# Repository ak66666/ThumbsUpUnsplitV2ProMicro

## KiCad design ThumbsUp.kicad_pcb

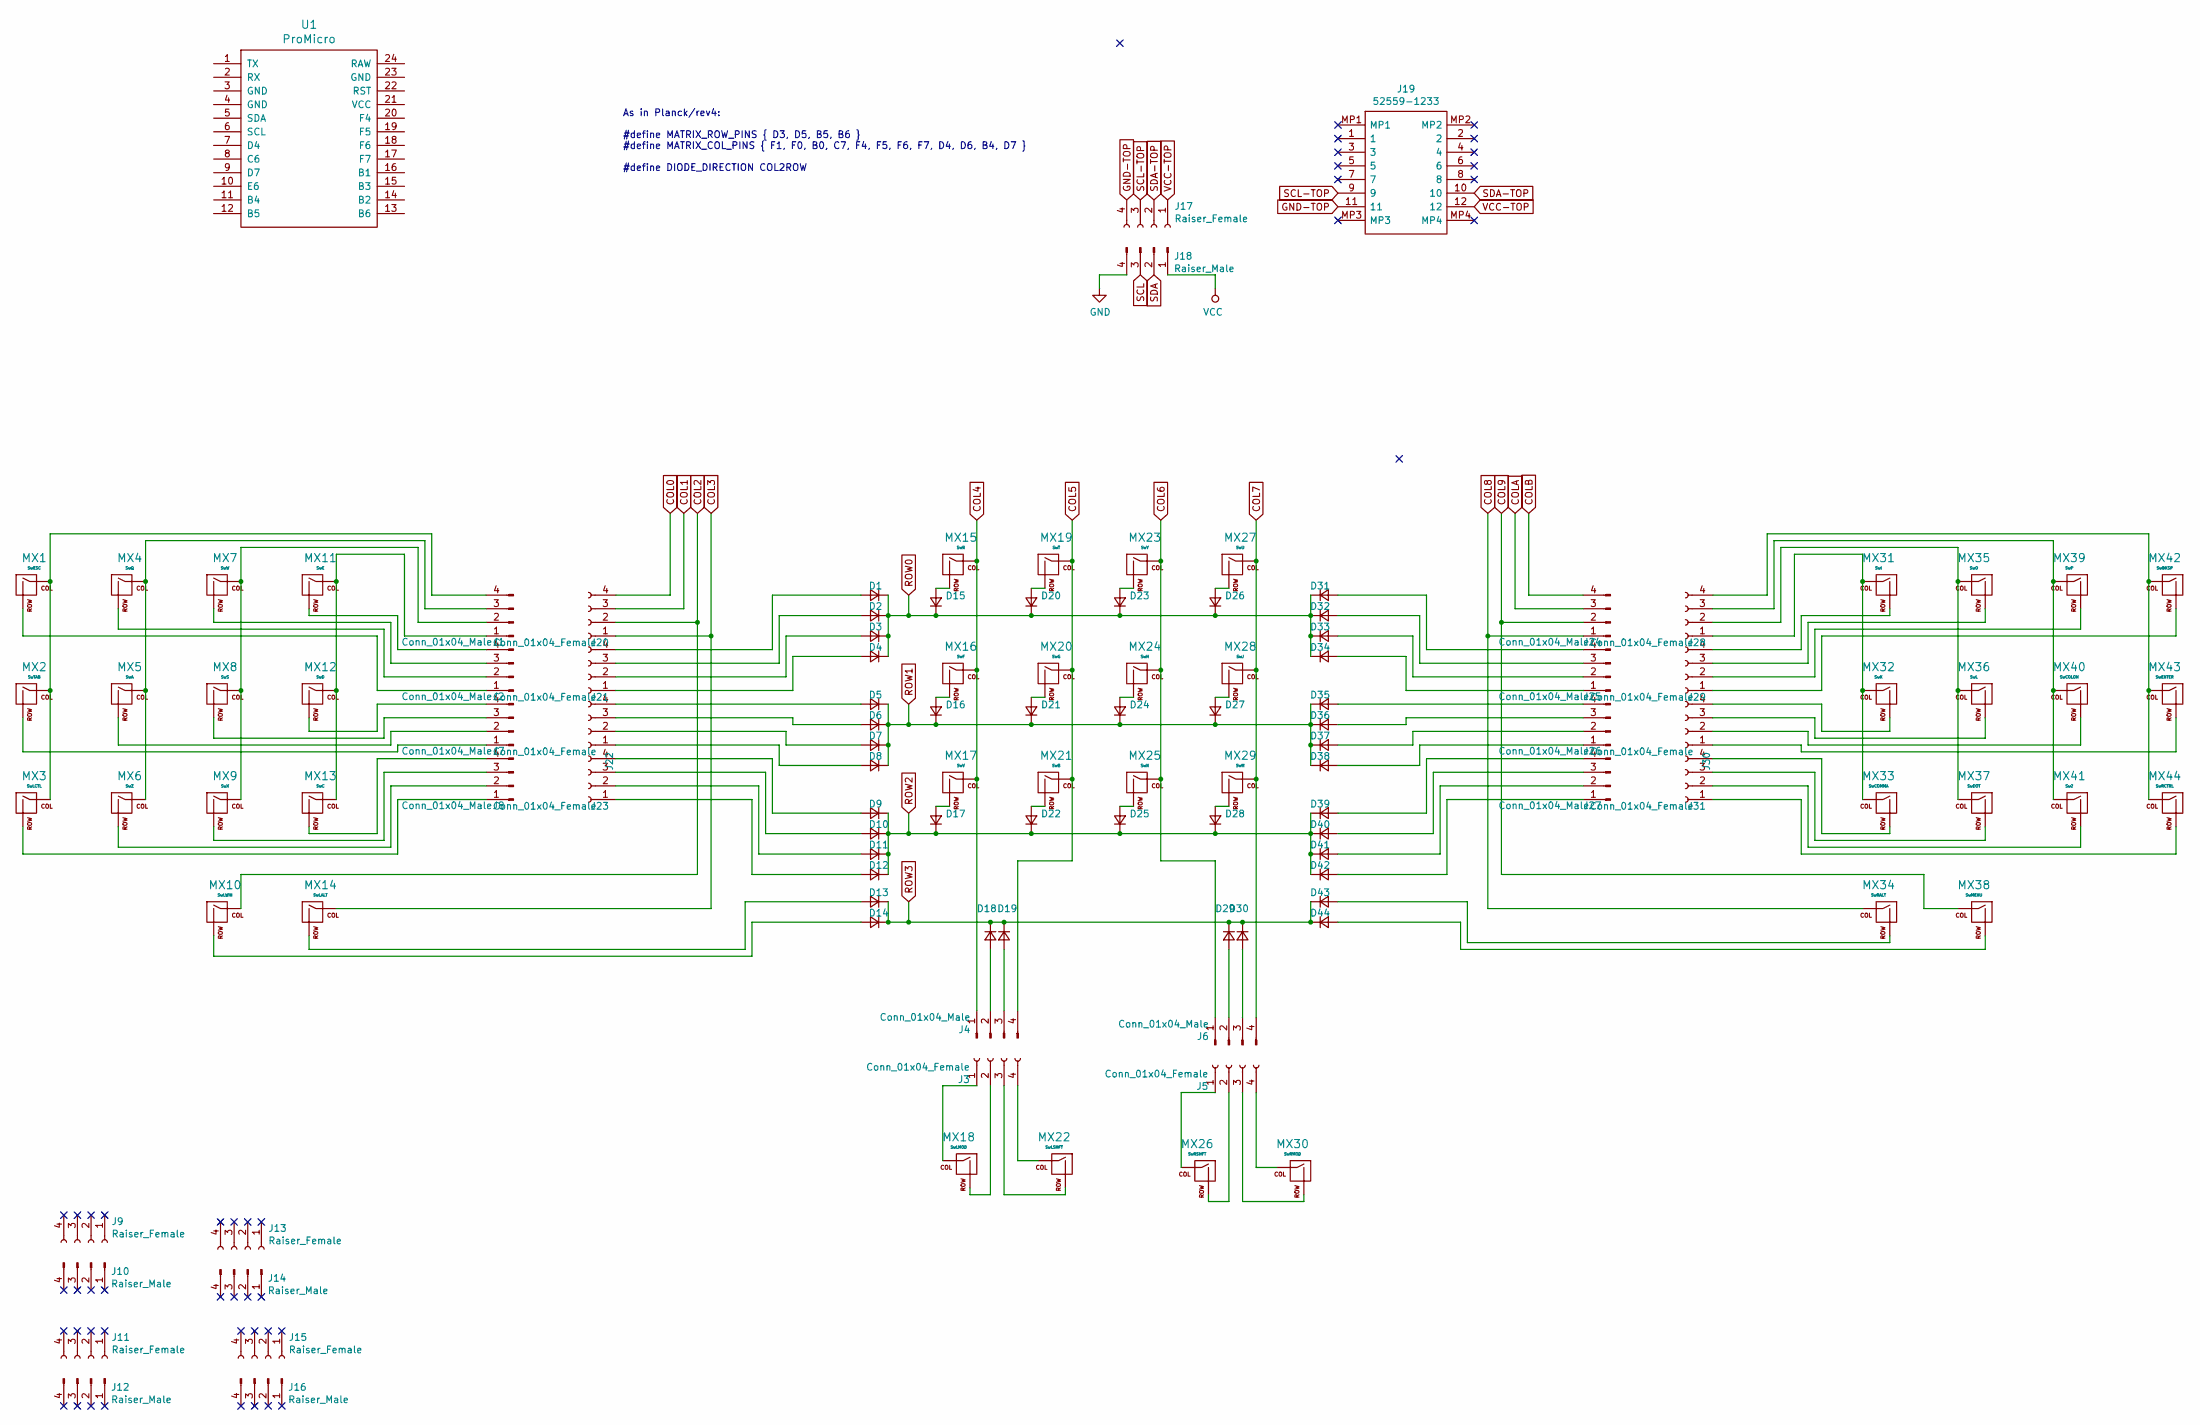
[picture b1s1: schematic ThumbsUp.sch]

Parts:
D1, D2, D3, D4, D5, D6, D7, D8, D9, D10, D11, D12, D13, D14, D15, D16, D17, D18, D19, D20, D21, D22, D23, D24, D25, D26, D27, D28, D29, D30, D31, D32, D33, D34, D35, D36, D37, D38, D39, D40, D41, D42, D43, D44: D_Small; D_SOD-123
J1, J2, J4, J6, J7, J8, J24, J25, J26, J27: Conn_01x04_Male; PinHeader_1x04_P2.54mm_Vertical
J3, J5, J20, J21, J22, J23, J28, J29, J30, J31: Conn_01x04_Female; PinSocket_1x04_P2.54mm_Vertical
J9, J11, J13, J15, J17: Raiser_Female; PinSocket_1x04_P2.54mm_Vertical
J10, J12, J14, J16, J18: Raiser_Male; PinHeader_1x04_P2.54mm_Vertical
J19: 52559-1233; 525591233; Mouser Part Number 538-52559-1233
MX1: SwESC; Kailh_socket_PG1350_optional
MX2: SwTAB; Kailh_socket_PG1350_optional
MX3: SwLCTL; Kailh_socket_PG1350_optional
MX4: SwQ; Kailh_socket_PG1350_optional
MX5: SwA; Kailh_socket_PG1350_optional
MX6: SwZ; Kailh_socket_PG1350_optional
MX7: SwW; Kailh_socket_PG1350_optional
MX8: SwS; Kailh_socket_PG1350_optional
MX9: SwX; Kailh_socket_PG1350_optional
MX10: SwLWIN; Kailh_socket_PG1350_optional
MX11: SwE; Kailh_socket_PG1350_optional
MX12: SwD; Kailh_socket_PG1350_optional
MX13: SwC; Kailh_socket_PG1350_optional
MX14: SwLALT; Kailh_socket_PG1350_optional
MX15: SwR; Kailh_socket_PG1350_optional
MX16: SwF; Kailh_socket_PG1350_optional
MX17: SwV; Kailh_socket_PG1350_optional
MX18: SwLMOD; Kailh_socket_PG1350_optional
MX19: SwT; Kailh_socket_PG1350_optional
MX20: SwG; Kailh_socket_PG1350_optional
MX21: SwB; Kailh_socket_PG1350_optional
MX22: SwLSHFT; Kailh_socket_PG1350_optional
MX23: SwY; Kailh_socket_PG1350_optional
MX24: SwH; Kailh_socket_PG1350_optional
MX25: SwN; Kailh_socket_PG1350_optional
MX26: SwRSHFT; Kailh_socket_PG1350_optional
MX27: SwU; Kailh_socket_PG1350_optional
MX28: SwJ; Kailh_socket_PG1350_optional
MX29: SwM; Kailh_socket_PG1350_optional
MX30: SwRMOD; Kailh_socket_PG1350_optional
MX31: SwI; Kailh_socket_PG1350_optional
MX32: SwK; Kailh_socket_PG1350_optional
MX33: SwCOMMA; Kailh_socket_PG1350_optional
MX34: SwRALT; Kailh_socket_PG1350_optional
MX35: SwO; Kailh_socket_PG1350_optional
MX36: SwL; Kailh_socket_PG1350_optional
MX37: SwDOT; Kailh_socket_PG1350_optional
MX38: SwMENU; Kailh_socket_PG1350_optional
MX39: SwP; Kailh_socket_PG1350_optional
MX40: SwCOLON; Kailh_socket_PG1350_optional
MX41: Sw?; Kailh_socket_PG1350_optional
MX42: SwBKSP; Kailh_socket_PG1350_optional
MX43: SwENTER; Kailh_socket_PG1350_optional
MX44: SwRCTRL; Kailh_socket_PG1350_optional
U1: ProMicro

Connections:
COL0: J20.4, U1.14 (B2)
COL1: J20.3, U1.13 (B6)
COL2: J20.2, MX10.1 (COL), U1.12 (B5)
COL3: J20.1, MX14.1 (COL), U1.11 (B4)
COL4: J4.1, MX15.1 (COL), MX16.1 (COL), MX17.1 (COL), U1.10 (E6)
COL5: J4.4, MX19.1 (COL), MX20.1 (COL), MX21.1 (COL), U1.9 (D7)
COL6: J6.1, MX23.1 (COL), MX24.1 (COL), MX25.1 (COL), U1.15 (B3)
COL7: J6.4, MX27.1 (COL), MX28.1 (COL), MX29.1 (COL), U1.20 (F4)
COL8: J24.1, MX34.1 (COL), U1.19 (F5)
COL9: J24.2, MX38.1 (COL), U1.18 (F6)
COLA: J24.3, U1.17 (F7)
COLB: J24.4, U1.16 (B1)
GND: J18.4, U1.23 (GND); also elsewhere on the board
GND-TOP: J17.4, J19.11
unnamed: D1.2 (A), J21.4
unnamed: D2.2 (A), J21.3
unnamed: D3.2 (A), J21.2
unnamed: D4.2 (A), J21.1
unnamed: D5.2 (A), J22.4
unnamed: D6.2 (A), J22.3
unnamed: D7.2 (A), J22.2
unnamed: D8.2 (A), J22.1
unnamed: D9.2 (A), J23.4
unnamed: D10.2 (A), J23.3
unnamed: D11.2 (A), J23.2
unnamed: D12.2 (A), J23.1
unnamed: D13.2 (A), MX14.2 (ROW)
unnamed: D14.2 (A), MX10.2 (ROW)
unnamed: D15.2 (A), MX15.2 (ROW)
unnamed: D16.2 (A), MX16.2 (ROW)
unnamed: D17.2 (A), MX17.2 (ROW)
unnamed: D18.2 (A), J4.2
unnamed: D19.2 (A), J4.3
unnamed: D20.2 (A), MX19.2 (ROW)
unnamed: D21.2 (A), MX20.2 (ROW)
unnamed: D22.2 (A), MX21.2 (ROW)
unnamed: D23.2 (A), MX23.2 (ROW)
unnamed: D24.2 (A), MX24.2 (ROW)
unnamed: D25.2 (A), MX25.2 (ROW)
unnamed: D26.2 (A), MX27.2 (ROW)
unnamed: D27.2 (A), MX28.2 (ROW)
unnamed: D28.2 (A), MX29.2 (ROW)
unnamed: D29.2 (A), J6.2
unnamed: D30.2 (A), J6.3
unnamed: D31.2 (A), J25.4
unnamed: D32.2 (A), J25.3
unnamed: D33.2 (A), J25.2
unnamed: D34.2 (A), J25.1
unnamed: D35.2 (A), J26.4
unnamed: D36.2 (A), J26.3
unnamed: D37.2 (A), J26.2
unnamed: D38.2 (A), J26.1
unnamed: D39.2 (A), J27.4
unnamed: D40.2 (A), J27.3
unnamed: D41.2 (A), J27.2
unnamed: D42.2 (A), J27.1
unnamed: D43.2 (A), MX34.2 (ROW)
unnamed: D44.2 (A), MX38.2 (ROW)
unnamed: J1.1, MX11.1 (COL), MX12.1 (COL), MX13.1 (COL)
unnamed: J1.2, MX7.1 (COL), MX8.1 (COL), MX9.1 (COL)
unnamed: J1.3, MX4.1 (COL), MX5.1 (COL), MX6.1 (COL)
unnamed: J1.4, MX1.1 (COL), MX2.1 (COL), MX3.1 (COL)
unnamed: J2.1, MX1.2 (ROW)
unnamed: J2.2, MX4.2 (ROW)
unnamed: J2.3, MX7.2 (ROW)
unnamed: J2.4, MX11.2 (ROW)
unnamed: J3.1, MX18.1 (COL)
unnamed: J3.2, MX18.2 (ROW)
unnamed: J3.3, MX22.2 (ROW)
unnamed: J3.4, MX22.1 (COL)
unnamed: J5.1, MX26.1 (COL)
unnamed: J5.2, MX26.2 (ROW)
unnamed: J5.3, MX30.2 (ROW)
unnamed: J5.4, MX30.1 (COL)
unnamed: J7.1, MX2.2 (ROW)
unnamed: J7.2, MX5.2 (ROW)
unnamed: J7.3, MX8.2 (ROW)
unnamed: J7.4, MX12.2 (ROW)
unnamed: J8.1, MX3.2 (ROW)
unnamed: J8.2, MX6.2 (ROW)
unnamed: J8.3, MX9.2 (ROW)
unnamed: J8.4, MX13.2 (ROW)
unnamed: J28.1, MX31.1 (COL), MX32.1 (COL), MX33.1 (COL)
unnamed: J28.2, MX35.1 (COL), MX36.1 (COL), MX37.1 (COL)
unnamed: J28.3, MX39.1 (COL), MX40.1 (COL), MX41.1 (COL)
unnamed: J28.4, MX42.1 (COL), MX43.1 (COL), MX44.1 (COL)
unnamed: J29.1, MX42.2 (ROW)
unnamed: J29.2, MX39.2 (ROW)
unnamed: J29.3, MX35.2 (ROW)
unnamed: J29.4, MX31.2 (ROW)
unnamed: J30.1, MX43.2 (ROW)
unnamed: J30.2, MX40.2 (ROW)
unnamed: J30.3, MX36.2 (ROW)
unnamed: J30.4, MX32.2 (ROW)
unnamed: J31.1, MX44.2 (ROW)
unnamed: J31.2, MX41.2 (ROW)
unnamed: J31.3, MX37.2 (ROW)
unnamed: J31.4, MX33.2 (ROW)
ROW0: D1.1 (K), D2.1 (K), D3.1 (K), D4.1 (K), D15.1 (K), D20.1 (K), D23.1 (K), D26.1 (K), D31.1 (K), D32.1 (K), D33.1 (K), D34.1 (K), U1.1 (TX)
ROW1: D5.1 (K), D6.1 (K), D7.1 (K), D8.1 (K), D16.1 (K), D21.1 (K), D24.1 (K), D27.1 (K), D35.1 (K), D36.1 (K), D37.1 (K), D38.1 (K), U1.2 (RX)
ROW2: D9.1 (K), D10.1 (K), D11.1 (K), D12.1 (K), D17.1 (K), D22.1 (K), D25.1 (K), D28.1 (K), D39.1 (K), D40.1 (K), D41.1 (K), D42.1 (K), U1.7 (D4)
ROW3: D13.1 (K), D14.1 (K), D18.1 (K), D19.1 (K), D29.1 (K), D30.1 (K), D43.1 (K), D44.1 (K), U1.8 (C6)
RST: U1.22 (RST); also elsewhere on the board
SCL: J18.3, U1.6 (SCL); also elsewhere on the board
SCL-TOP: J17.3, J19.9
SDA: J18.2, U1.5 (SDA); also elsewhere on the board
SDA-TOP: J17.2, J19.10
VCC: J18.1, U1.21 (VCC); also elsewhere on the board
VCC-TOP: J17.1, J19.12

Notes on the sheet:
As in Planck/rev4: #define MATRIX_ROW_PINS { D3, D5, B5, B6 } #define MATRIX_COL_PINS { F1, F0, B0, C7, F4, F5, F6, F7, D4, D6, B4, D7 } #define DIODE_DIRECTION COL2ROW

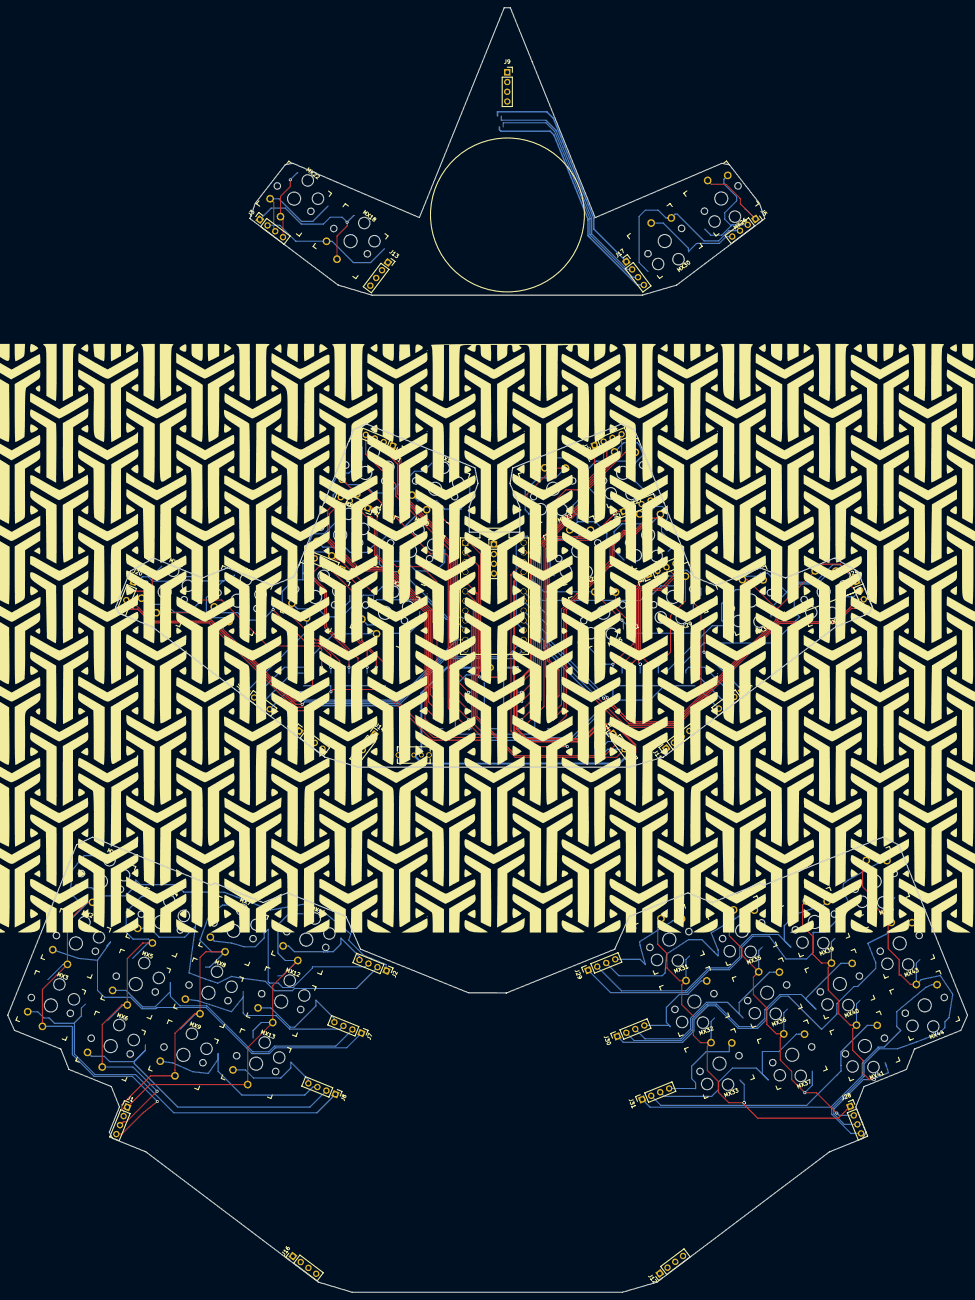
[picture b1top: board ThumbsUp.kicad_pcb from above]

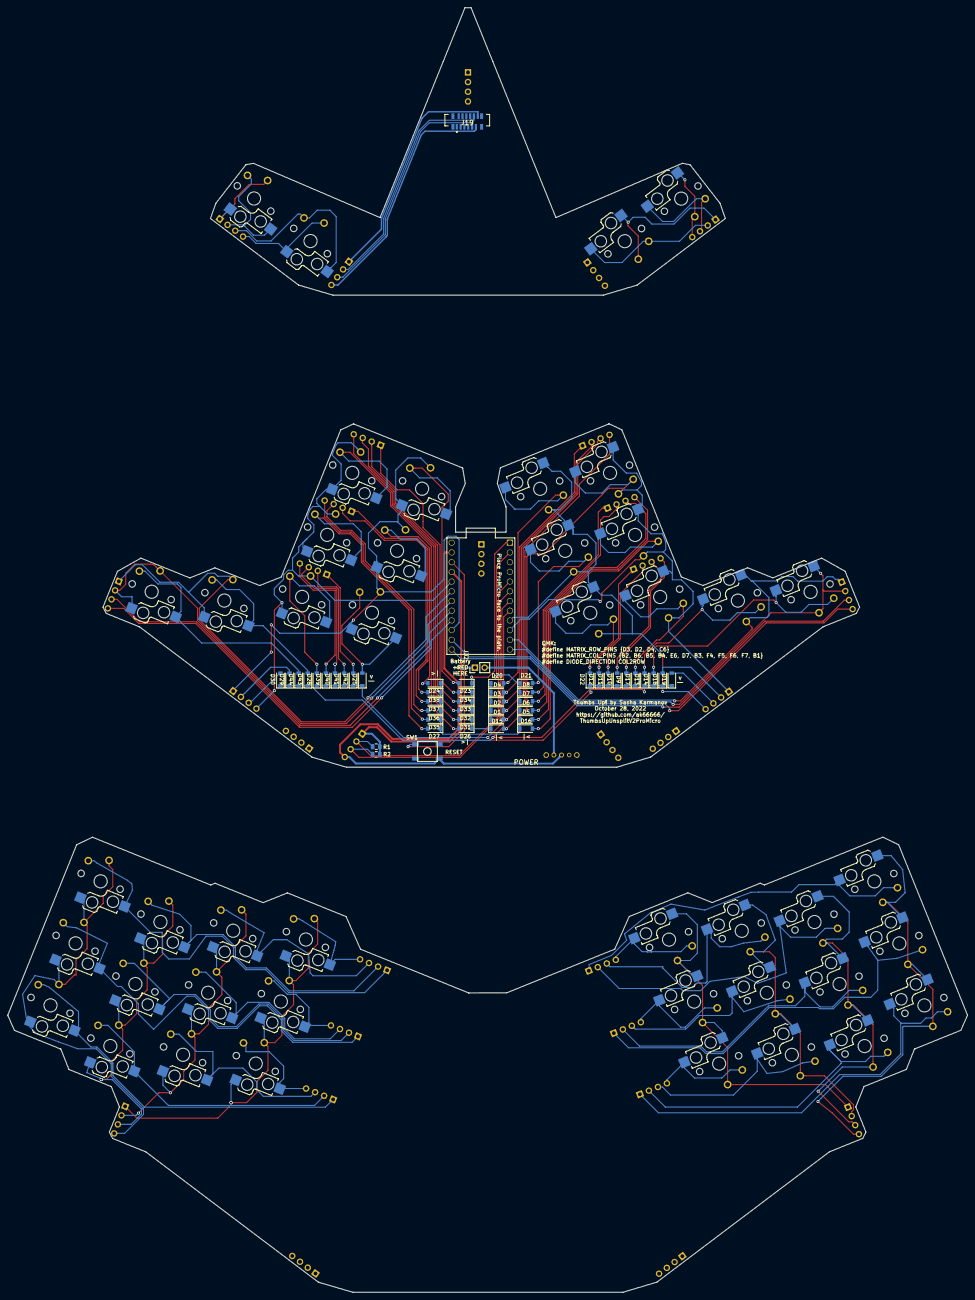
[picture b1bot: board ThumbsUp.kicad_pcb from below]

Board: 2 copper layers, 251.1 x 336.1 mm, 125 parts (49 on the bottom side), 110 nets.

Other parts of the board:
J32: Battery; PinHeader_1x02_P2.54mm_Vertical
POWER: SW_DIP_x01; 18252321
R1, R2: 5.1K; R_0805_2012Metric
SW1: SW_Push; SKQG-1155865

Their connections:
GND: POWER.2, SW1.2; also elsewhere on the board
unnamed: J32.2, POWER.1
RST: SW1.1; also elsewhere on the board
SCL: R1.1; also elsewhere on the board
SDA: R2.2; also elsewhere on the board
VCC: J32.1, R1.2, R2.1; also elsewhere on the board

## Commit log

2022-11-11 Cloned the v2 project to use ProMicro instead of the separate McU
2022-11-12 Routed the second layer, prepared for plotting
2022-12-17 Added power connector, pullup resistors for the trackpad, made the promicro holes bigger to fit the sockets.
2022-12-18 Regenerated Gerber for the middle layer.
